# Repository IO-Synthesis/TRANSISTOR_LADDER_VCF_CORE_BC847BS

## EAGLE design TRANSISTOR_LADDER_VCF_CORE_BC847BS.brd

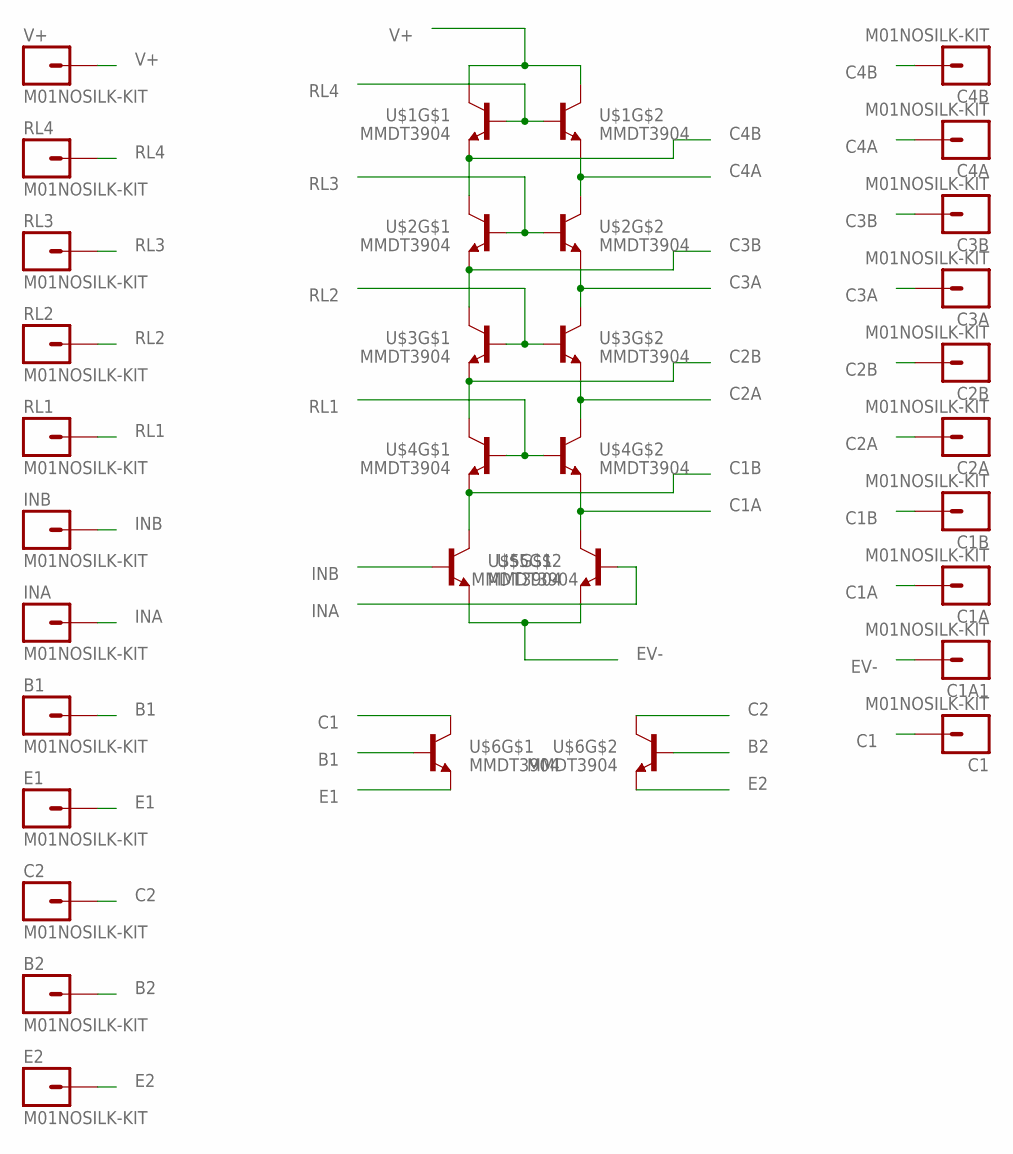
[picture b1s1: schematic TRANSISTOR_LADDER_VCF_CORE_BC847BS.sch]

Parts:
B1, B2: M01NOSILK-KIT; 1X01NS-KIT
C1, C1A, C1A1, C1B, C2, C2A, C2B, C3A, C3B, C4A, C4B: M01NOSILK-KIT; 1X01NS-KIT
E1, E2: M01NOSILK-KIT; 1X01NS-KIT
INA: M01NOSILK-KIT; 1X01NS-KIT
INB: M01NOSILK-KIT; 1X01NS-KIT
RL1, RL2, RL3, RL4: M01NOSILK-KIT; 1X01NS-KIT
U$1, U$2, U$3, U$4, U$5, U$6: MMDT3904; SOT363
V+: M01NOSILK-KIT; 1X01NS-KIT

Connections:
B1: B1.1, U$6.2 (B)
B2: B2.1, U$6.5 (B)
C1: C1.1, U$6.6 (C)
C1A: C1A.1, U$4.1 (E), U$5.6 (C)
C1B: C1B.1, U$4.4 (E), U$5.3 (C)
C2: C2.1, U$6.3 (C)
C2A: C2A.1, U$3.1 (E), U$4.6 (C)
C2B: C2B.1, U$3.4 (E), U$4.3 (C)
C3A: C3A.1, U$2.1 (E), U$3.6 (C)
C3B: C3B.1, U$2.4 (E), U$3.3 (C)
C4A: C4A.1, U$1.1 (E), U$2.6 (C)
C4B: C4B.1, U$1.4 (E), U$2.3 (C)
E1: E1.1, U$6.1 (E)
E2: E2.1, U$6.4 (E)
EV-: C1A1.1, U$5.1 (E), U$5.4 (E)
INA: INA.1, U$5.2 (B)
INB: INB.1, U$5.5 (B)
RL1: RL1.1, U$4.2 (B), U$4.5 (B)
RL2: RL2.1, U$3.2 (B), U$3.5 (B)
RL3: RL3.1, U$2.2 (B), U$2.5 (B)
RL4: RL4.1, U$1.2 (B), U$1.5 (B)
V+: U$1.3 (C), U$1.6 (C), V+.1

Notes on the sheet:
EV-
RL4
RL3
RL2
RL1
INB
INA
C4B
C4A
C3B
C3A
C2B
C2A
C1B
C1A

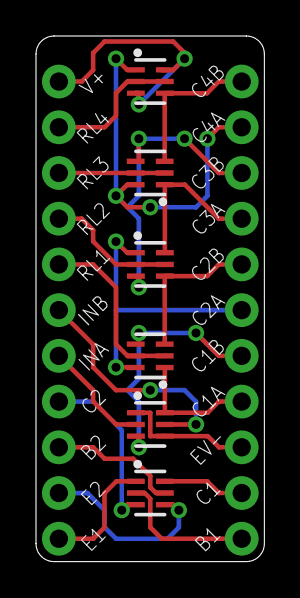
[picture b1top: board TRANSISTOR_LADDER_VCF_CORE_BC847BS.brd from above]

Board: 2 copper layers, 12.7 x 29.2 mm, 28 parts (0 on the bottom side), 22 nets.

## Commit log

2017-01-09 :octocat: Added .gitattributes & .gitignore files
2017-01-09 TRANSISTOR_LADDER_VCF_CORE_BC847BS
    TRANSISTOR_LADDER_VCF_CORE_BC847BS
2017-01-09 TRANSISTOR_LADDER_VCF_CORE

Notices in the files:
parts and their libraries:
SparkFun-Connectors: Licensing: Creative Commons ShareAlike 4.0 International - https://creativecommons.org/licenses/by-sa/4.0
